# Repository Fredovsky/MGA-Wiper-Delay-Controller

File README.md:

# Classic Car Intermittent Wiper Motor Controller

A fully customizable, Arduino-based, multi-frequency intermittent wiper controller for classic British cars with single-speed Lucas DR2 wiper motors. This controller is non-destructive and fully reversible, requiring no modifications to the original vehicle.

## Overview

Some classic British cars such as the MG MGA and Triumph TR2 came equipped with a single-speed Lucas DR2 wiper motor. When encountering rain of various intensity, the single speed is just not appropriate 90% of the time. This project provides an intelligent controller that adds intermittent wiper functionality without modifying the original vehicle or requiring additional switches.

### Key Features

- **Non-destructive installation** - No modifications to the original vehicle
- **Uses factory switch** - No need for additional controls or multi-position switches
- **Multiple intermittent speeds** - Four configurable delay settings plus continuous mode
- **Intuitive control** - Quick ON-OFF-ON toggles to cycle through speeds
- **Compact design** - Small SMD-based PCB fits under the dashboard
- **Arduino-based** - Easy to program and customize
- **Fully reversible** - Can be removed and wiring restored to factory configuration

## The Problem

The Lucas DR2 wiper motor found in many classic British cars from the 1950s and 1960s operates at only a single, continuous speed. When driving through light rain at moderate/slow speeds, this continuous wiping motion is often too frequent. Many drivers end up manually switching the wipers ON and OFF repeatedly to achieve the desired intermittent wiping - this project automates that process.

### Original Wiper System

The factory wiper system has three terminals:
- **Terminal 2**: Continuous +12V power
- **Terminal 1**: Ground connection via dashboard switch
- **Terminal E**: Auto-parking ground connection

When the dashboard switch grounds terminal 1, the motor starts. The motor continues running via terminal E until the wipers return to their parked position, regardless of the switch position. If the switch is still closed when parked, wiping continues; otherwise, the motor stops.

## Solution

This controller sits between the original dashboard switch and the wiper motor, interpreting the switch position to provide multiple intermittent wiper modes. The driver uses quick ON-OFF-ON toggles of the original switch to cycle through different intermittent speeds.

### Operation Modes

The controller provides five operating modes:

1. **Intermittent 1**: Wipes every 10 seconds (slowest)
2. **Intermittent 2**: Wipes every 7.5 seconds
3. **Intermittent 3**: Wipes every 5 seconds
4. **Intermittent 4**: Wipes every 2.5 seconds
5. **Continuous**: Original single-speed operation (fastest)

### User Interface

- **Activate wipers**: Pull the switch ON to start wipers at the slowest intermittent setting
- **Increase speed**: Quickly toggle the switch OFF then ON (within 2 seconds) to advance to the next faster setting
- **Turn off wipers**: Push the switch OFF and hold for more than 2 seconds to deactivate and reset
- **Next activation**: Always starts at the slowest intermittent setting after a reset

## Hardware Design

### Architecture

The controller consists of three main sections:

1. **Power Regulation**: 12V to 5V conversion for microcontroller operation
2. **Microcontroller**: ATtiny85 running Arduino framework code
3. **Relay Driver**: High-current relay to control the wiper motor (5-10A capability)

### Components

#### Main Components

| Component | Part Number | Description | Quantity |
|-----------|-------------|-------------|----------|
| **Microcontroller** | ATtiny85-20SU | 8-bit MCU, 8K Flash, Arduino compatible | 1 |
| **Voltage Regulator** | LM2931DT-5.0G | 5V 100mA LDO with load dump protection | 1 |
| **Relay** | V23076A1001C133 | Automotive power relay | 1 |
| **Transistor** | BC846BLT1G | NPN transistor for relay driver | 1 |
| **Optocoupler** | SFH6186-3T | Isolation for switch input | 1 |

#### Passive Components

| Component | Part Number | Description | Quantity |
|-----------|-------------|-------------|----------|
| **Ferrite Beads** | FBMJ2125HS420-T | 0805 42Ω current chip bead | 2 |
| **Rectifier Diodes** | CGRTS4007-HF | 1000V 1A SMD rectifier | 2 |
| **Zener Diode** | SZMMSZ33ET1G | 33V 0.5W voltage regulator | 1 |
| **C1** | C0603C473K3RACTU | 0.047µF 25V X7R 0603 | 1 |
| **C2** | CGA4J1X7S1E106K125AC | 10µF 25V 0805 | 1 |
| **C3** | GRM21BC71C106KE11L | 10µF 16V X7S 0805 | 1 |
| **C4** | 35ZLH100MEFC6.3X11 | 100µF electrolytic capacitor | 1 |
| **C5, C6** | C0603C104K3RAC3190 | 0.1µF 25V X7R 0603 | 2 |
| **R1** | CRGP2512F470R | 470Ω 1% 2512 SMD | 1 |
| **R2, R3** | ERJ-3EKF1002V | 10kΩ 1% 0603 | 2 |
| **R4** | ERJ-3EKF1001V | 1kΩ 1% 0603 | 1 |

#### Connectors

| Component | Part Number | Description | Quantity |
|-----------|-------------|-------------|----------|
| **J1-J4** | 7799 | M4 screw terminals | 4 |
| **J5** | 10129381-906004BLF | 2×3 ISP programming header | 1 |

### PCB Design

The PCB uses primarily SMD components to minimize size and was designed to potentially mount directly to the wiper motor housing. The final implementation installs under the dashboard where it remains virtually invisible while maintaining the stock appearance of the vehicle.

**PCB Specifications:**
- Compact two-layer design
- SMD components (0603/0805) where possible
- Through-hole components for high-current connections
- ISP programming header for easy firmware updates

### Enclosure

The controller is housed in a two-part snap-fit enclosure designed in Fusion 360. Originally intended to mount on the wiper motor housing, the final installation places it under the dashboard for easier access and installation.

## Software

The controller is programmed using the Arduino framework with the ATtiny85 core. The code implements:

- **Switch debouncing** in software (50ms delay)
- **Non-blocking timing** using `millis()` instead of `delay()`
- **Toggle detection** to cycle through intermittent speeds

### Key Parameters

```cpp
// I/O Configuration
#define PIN_WIPER_OUTPUT 3          // Relay control pin
#define PIN_INPUT_SWITCH 4          // Dashboard switch input pin
#define SWITCH_DEBOUNCE_DELAY_MS 50 // Debounce delay
#define TOGGLE_LIMIT_DELAY 2000     // Max time for toggle detection

// Intermittent Delays
#define INTERMITTENT_1_MS 10000     // 10 seconds
#define INTERMITTENT_2_MS 7500      // 7.5 seconds
#define INTERMITTENT_3_MS 5000      // 5 seconds
#define INTERMITTENT_4_MS 2500      // 2.5 seconds

// Motor Control
#define RELAY_TIME_MS 500           // Relay activation duration
```

### Software Architecture

The software consists of two main functions:

#### `loop()` Function
- Reads the dashboard switch state
- Implements software debouncing
- Detects state changes (ON→OFF, OFF→ON)
- Tracks toggle sequences to determine mode changes

#### `wipe()` Function
- Executes wiper control based on current mode
- Manages timing for intermittent delays
- Controls relay activation/deactivation

### Customization

The intermittent delays can be easily customized by modifying the `INTERMITTENT_X_MS` definitions. The values are in milliseconds, so adjusting them to your preference is straightforward.

## Installation

### Wiring

The controller installs inline between the original wiring harness and the wiper motor:

**Input (from vehicle harness):**
- J1: Ground from dashboard switch
- J2: +12V power
- J3: Parking switch connection

**Output (to wiper motor):**
- J3: To motor terminal 1
- J2: To motor terminal 2 (through controller)
- J4: To motor terminal E

### Programming

The ATtiny85 can be programmed via the ISP header (J5) using:
- USBasp programmer
- Arduino as ISP
- Other AVR programmers supporting ISP protocol

Flash the provided Arduino sketch to the ATtiny85 using the ISP connector on the PCB.

### Physical Installation

1. Disconnect the battery negative terminal
2. Locate the wiper motor and disconnect the original three-wire connector
3. Connect the controller inline between the harness and motor
4. Mount the controller under the dashboard using zip ties or mounting brackets
5. Reconnect the battery and test operation

## Testing

After installation, verify operation:

1. **Power on**: Pull the wiper switch - wipers should activate in slowest intermittent mode
2. **Toggle test**: Quickly switch OFF then ON - wipers should advance to next speed
3. **All modes**: Cycle through all five modes to verify each speed
4. **Reset**: Hold switch OFF for 3+ seconds, then reactivate - should start at slowest speed
5. **Parking**: Turn off in any mode - wipers should return to parked position

## Performance

The controller has been successfully tested and installed in an MG MGA. Key observations:

- **Reliable operation**: No false triggers or missed toggles
- **Proper timing**: All intermittent delays work as programmed
- **Original functionality preserved**: Can be removed without trace
- **Invisible installation**: Maintains stock appearance

## Files and Resources

All project files are available in this repository:
- `PlatformIO/` - Arduino source code
- `Eagle/` - Schematics, PCB layouts (+Gerber files)
- `Enclosure/` - 3D printable enclosure designs (STL/STEP files)

## Bill of Materials

Complete BOM with supplier part numbers is available in the `Eagle/BOM_Wiper_Control.pdf` file. All components are readily available from Mouser Electronics and other major suppliers.

## Requirements

### Hardware Requirements
- Classic car with Lucas DR2 or similar single-speed wiper motor
- Original single-pole ON-OFF wiper switch
- 12V electrical system

### Software Requirements
- Arduino IDE or PlatformIO
- ATtiny core support (install via Board Manager)

### Programming Tools
- AVR programmer with ISP support (USBasp or Arduino ISP programmer)
- 6-pin ISP cable

## Design Considerations

### Non-Destructive Philosophy
Every aspect of this design prioritizes reversibility:
- No cutting or drilling of original components
- No permanent wiring modifications
- No changes to dashboard or switch
- Controller can be completely removed, returning vehicle to factory specification

### Automotive Environment
The design accounts for the harsh automotive environment:
- Load dump protection in voltage regulator
- Automotive-grade relay rated for motor inrush current
- Ferrite beads for EMI suppression
- Proper wire gauge for current handling

### Safety
- Relay rated well above motor current draw
- Fused power connection recommended
- Isolated optocoupler for switch input
- Zener diode for voltage spike protection

## Compatibility

This controller is designed for the Lucas DR2 wiper motor but should work with any single-speed wiper motor that uses a similar three-wire configuration with auto-parking functionality. Confirm your motor's wiring matches before installation.

**Known compatible vehicles:**
- MG MGA (1955-1962)
- Triumph TR2 (1953-1955)
- Triumph TR3 (1955-1962)
- Other British cars from the 1950s-1960s with Lucas DR2 motors

## Contributing

Contributions are welcome! If you've installed this controller in a different vehicle or made improvements to the design, please submit a pull request or open an issue.

## License

This project is licensed under the **Creative Commons Attribution-NonCommercial-ShareAlike 4.0 International License (CC BY-NC-SA 4.0)**.

### You are free to:
- **Share** — copy and redistribute the material in any medium or format
- **Adapt** — remix, transform, and build upon the material

### Under the following terms:
- **Attribution** — You must give appropriate credit, provide a link to the license, and indicate if changes were made
- **NonCommercial** — You may not use the material for commercial purposes
- **ShareAlike** — If you remix, transform, or build upon the material, you must distribute your contributions under the same license

### What this means:
✅ **Allowed:**
- Personal use and modifications
- Educational purposes
- Sharing with the classic car community
- Building your own controller for your vehicle
- Sharing improvements and modifications

❌ **Not Allowed:**
- Selling the controller or kits commercially
- Manufacturing for profit
- Including in commercial products or services
- Using the design in commercial automotive products

**Full License:** [CC BY-NC-SA 4.0](https://creativecommons.org/licenses/by-nc-sa/4.0/)

## Acknowledgments

- **MGAGuru** for excellent wiper motor documentation
- **Arduino community** for ATtiny85 core support
- **Hackaday.io community** for feedback and encouragement

## Author

Created by F. Lidove for the classic car community.

Hackaday.io Project: https://hackaday.io/project/175605-classic-car-intermittent-wiper-motor-controller

## Disclaimer

This modification involves working with automotive electrical systems. While designed to be safe and reversible, improper installation could potentially damage your vehicle's electrical system. Install at your own risk. The author assumes no liability for any damage resulting from the use of this design.

Always disconnect the battery before working on automotive electrical systems.

## Support

For questions, issues, or discussions:
- Open an issue on this GitHub repository
- Comment on the Hackaday.io project page

---

*Enjoy safer driving in light rain with your classic British car!*

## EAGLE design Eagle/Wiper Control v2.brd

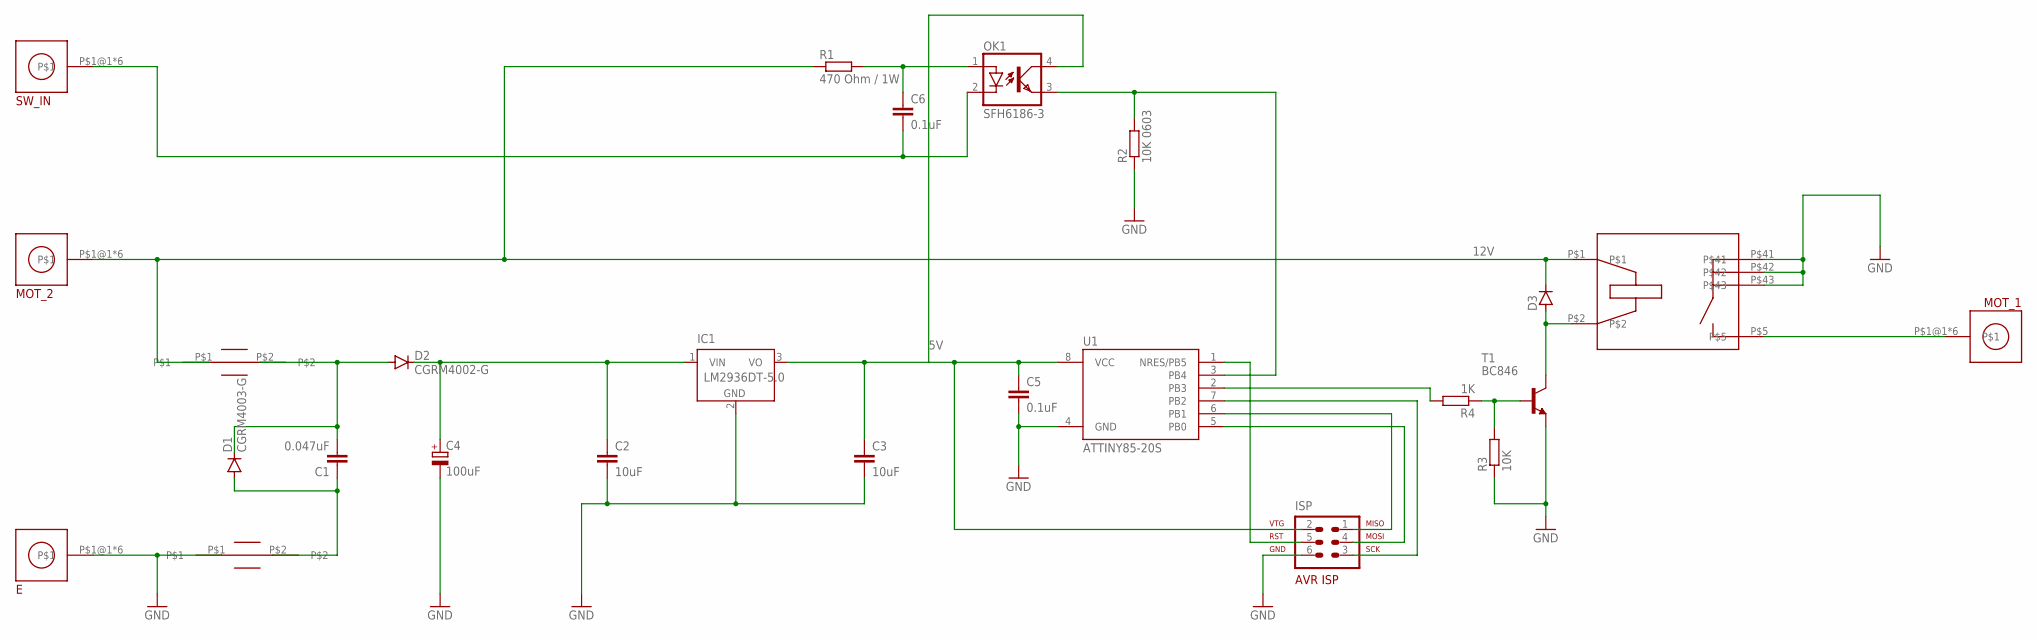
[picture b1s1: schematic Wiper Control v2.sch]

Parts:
B1, B2: FBMJ2125; FBMJ
C1: 0.047uF; C0603
C2, C3: 10uF; C0805
C4: 100uF; E2,5-7
C5, C6: 0.1uF; C0603
D1: CGRM4003-G; SOD-123_MINI-SMA
D2: CGRM4002-G; SOD-123_MINI-SMA
D3: D-SOD123; SOD123
E: M4_SCREW_TERMINAL
IC1: LM2936DT-5.0; TO252
ISP: AVR-ISP-6
MOT_1, MOT_2: M4_SCREW_TERMINAL
OK1: SFH6186-3; SMD4-7
R1: 470 Ohm / 1W; R2512
R2: 10K 0603; R0603
R3: 10K; R0603
R4: 1K; R0603
SW_IN: M4_SCREW_TERMINAL
T1: BC846; SOT23
U1: ATTINY85-20S; SOIC8_EIAJ_208MIL
U$3: RELAY

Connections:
5V: C3.1, C5.1, IC1.3 (VO), ISP.2, OK1.4 (COL), U1.8 (VCC)
12V: B1.P$1, D3.1 (C), MOT_2.P$1@1, MOT_2.P$1@2, MOT_2.P$1@3, MOT_2.P$1@4, MOT_2.P$1@5, MOT_2.P$1@6, R1.1, U$3.P$1
GND: B2.P$1, C2.2, C3.2, C4.-, C5.2, E.P$1@1, E.P$1@2, E.P$1@3, E.P$1@4, E.P$1@5, E.P$1@6, IC1.2 (GND), ISP.6, R2.1, R3.1, T1.2 (E), U1.4 (GND), U$3.P$41, U$3.P$42, U$3.P$43
unnamed: B1.P$2, C1.2, D1.C, D2.A
unnamed: B2.P$2, C1.1, D1.A
unnamed: C2.1, C4.+, D2.C, IC1.1 (VIN)
unnamed: ISP.1, U1.6 (PB1)
unnamed: ISP.4, U1.5 (PB0)
unnamed: ISP.3, U1.7 (PB2)
unnamed: ISP.5, U1.1 (NRES/PB5)
unnamed: D3.2 (A), T1.3 (C), U$3.P$2
unnamed: R3.2, R4.1, T1.1 (B)
unnamed: MOT_1.P$1@1, MOT_1.P$1@2, MOT_1.P$1@3, MOT_1.P$1@4, MOT_1.P$1@5, MOT_1.P$1@6, U$3.P$5
unnamed: C6.1, OK1.1 (A), R1.2
unnamed: OK1.3 (EMIT), R2.2, U1.3 (PB4)
unnamed: R4.2, U1.2 (PB3)
unnamed: C6.2, OK1.2 (C), SW_IN.P$1@1, SW_IN.P$1@2, SW_IN.P$1@3, SW_IN.P$1@4, SW_IN.P$1@5, SW_IN.P$1@6

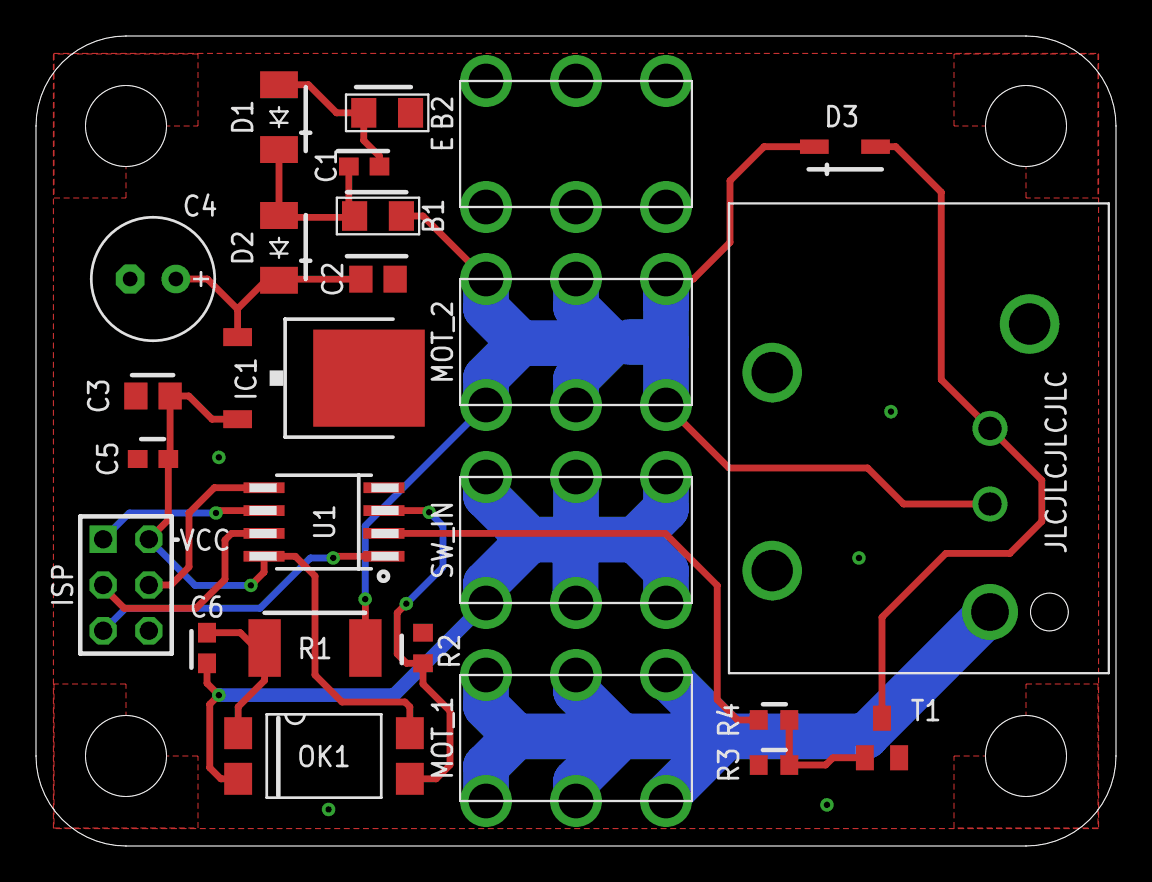
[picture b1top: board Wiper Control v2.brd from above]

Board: 2 copper layers, 60.0 x 45.0 mm, 25 parts (1 on the bottom side), 17 nets.

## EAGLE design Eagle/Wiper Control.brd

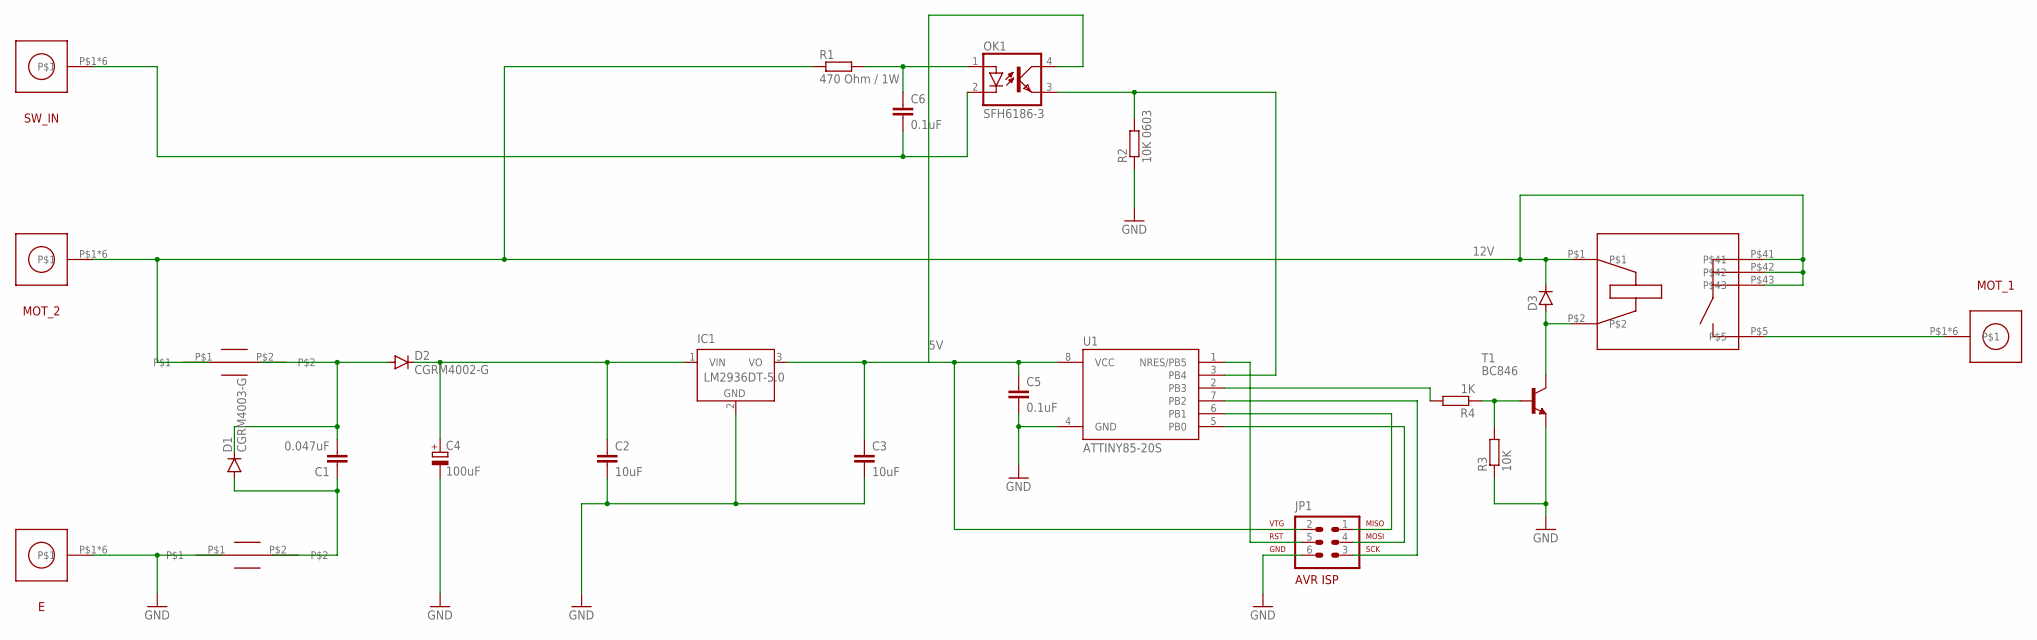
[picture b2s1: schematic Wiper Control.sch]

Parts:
C1: 0.047uF; C0603
C2, C3: 10uF; C0805
C4: 100uF; E2,5-7
C5, C6: 0.1uF; C0603
D1: CGRM4003-G; SOD-123_MINI-SMA
D2: CGRM4002-G; SOD-123_MINI-SMA
D3: D-SOD123; SOD123
E: M5_SCREW_TERMINAL
IC1: LM2936DT-5.0; TO252
JP1: AVR-ISP-6
MOT_1, MOT_2: M5_SCREW_TERMINAL
OK1: SFH6186-3; SMD4-7
R1: 470 Ohm / 1W; R2512
R2: 10K 0603; R0603
R3: 10K; R0603
R4: 1K; R0603
SW_IN: M5_SCREW_TERMINAL
T1: BC846; SOT23
U1: ATTINY85-20S; SOIC8_EIAJ_208MIL
U$1, U$2: FBMJ2125; FBMJ
U$3: RELAY

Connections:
5V: C3.1, C5.1, IC1.3 (VO), JP1.2, OK1.4 (COL), U1.8 (VCC)
12V: D3.1 (C), MOT_2.P$1, MOT_2.P$2, MOT_2.P$3, MOT_2.P$4, MOT_2.P$5, MOT_2.P$6, R1.1, U$1.P$1, U$3.P$1, U$3.P$41, U$3.P$42, U$3.P$43
GND: C2.2, C3.2, C4.-, C5.2, E.P$1, E.P$2, E.P$3, E.P$4, E.P$5, E.P$6, IC1.2 (GND), JP1.6, R2.1, R3.1, T1.2 (E), U1.4 (GND), U$2.P$1
unnamed: C1.2, D1.C, D2.A, U$1.P$2
unnamed: C1.1, D1.A, U$2.P$2
unnamed: C2.1, C4.+, D2.C, IC1.1 (VIN)
unnamed: JP1.1, U1.6 (PB1)
unnamed: JP1.4, U1.5 (PB0)
unnamed: JP1.3, U1.7 (PB2)
unnamed: JP1.5, U1.1 (NRES/PB5)
unnamed: D3.2 (A), T1.3 (C), U$3.P$2
unnamed: R3.2, R4.1, T1.1 (B)
unnamed: MOT_1.P$1, MOT_1.P$2, MOT_1.P$3, MOT_1.P$4, MOT_1.P$5, MOT_1.P$6, U$3.P$5
unnamed: C6.1, OK1.1 (A), R1.2
unnamed: OK1.3 (EMIT), R2.2, U1.3 (PB4)
unnamed: R4.2, U1.2 (PB3)
unnamed: C6.2, OK1.2 (C), SW_IN.P$1, SW_IN.P$2, SW_IN.P$3, SW_IN.P$4, SW_IN.P$5, SW_IN.P$6

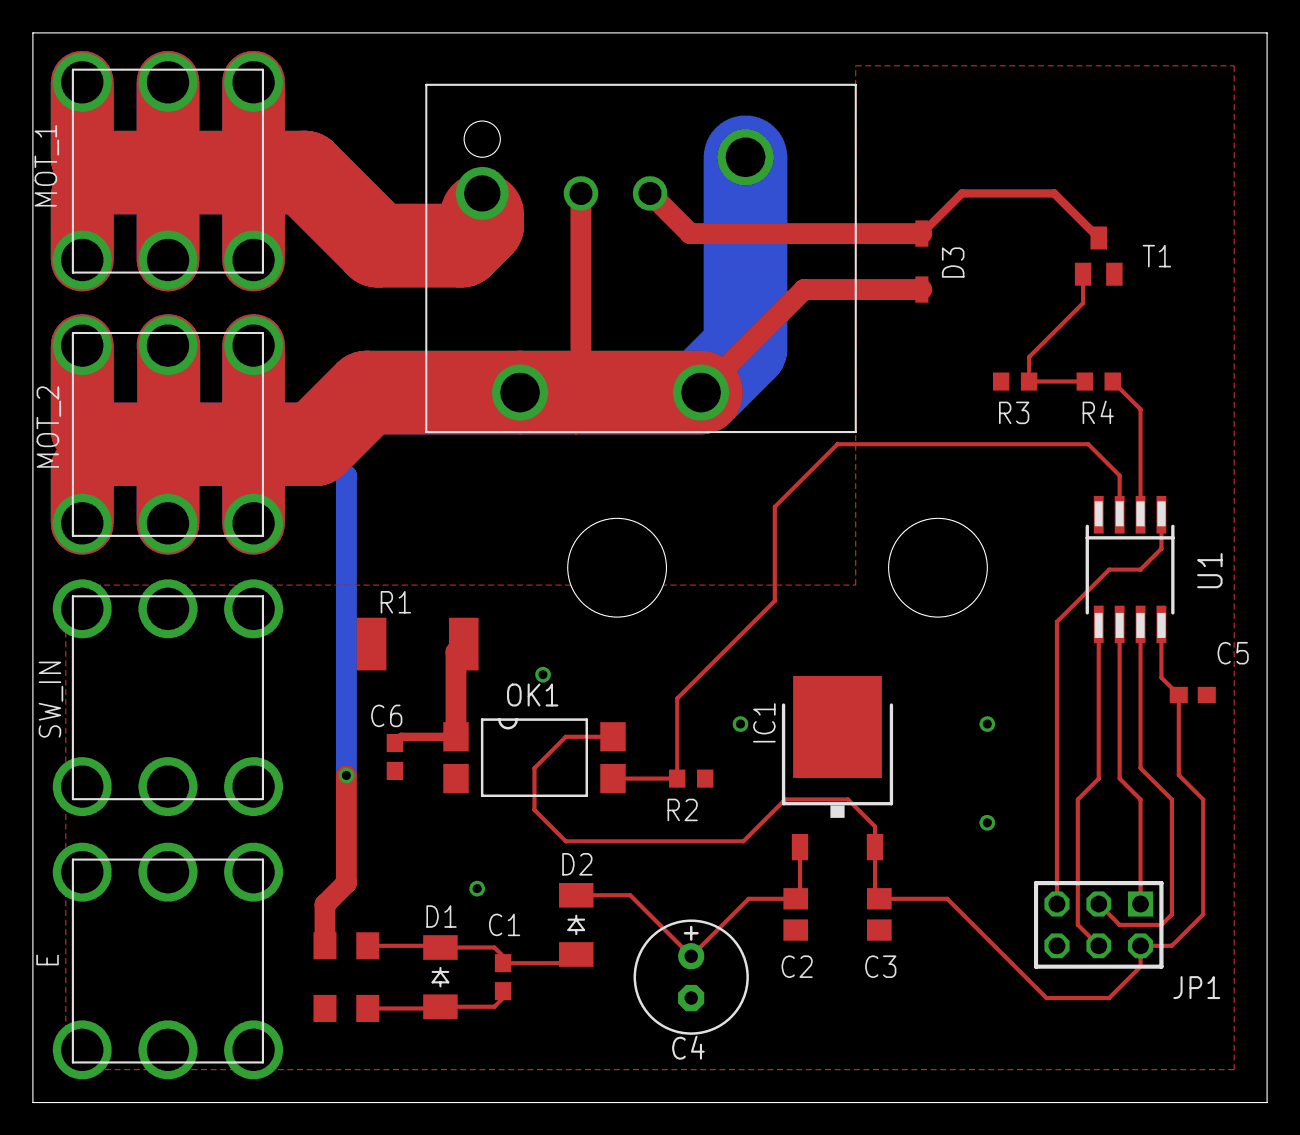
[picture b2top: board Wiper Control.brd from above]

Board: 2 copper layers, 75.0 x 65.0 mm, 25 parts (0 on the bottom side), 17 nets.

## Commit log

2021-03-23 Project creation.
    All files added. 3D printed box files on Fusion 360 cloud account.
2025-11-10 Add files via upload
    BOM added
2025-11-11 Add project details link to README
    Added project details link to README.
2025-11-11 Revise README for Classic Car Wiper Controller
    Updated project details and expanded documentation for the Classic Car Intermittent Wiper Motor Controller, including installation instructions, hardware design, software architecture, and safety con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
2025-11-11 Add video link to README overview section
    Added a video link to the project overview.
2025-11-11 Update BOM file location in README
    Updated BOM location from hardware/BOM.csv to Eagle/BOM_Wiper_Control.pdf.
2025-11-11 Clarify project license details in README
    Updated the license section to specify the Creative Commons Attribution-NonCommercial-ShareAlike 4.0 International License, including allowed and not allowed uses.
2025-11-12 Revise README for clarity and consistency
    Updated README to refine language and enhance clarity.
